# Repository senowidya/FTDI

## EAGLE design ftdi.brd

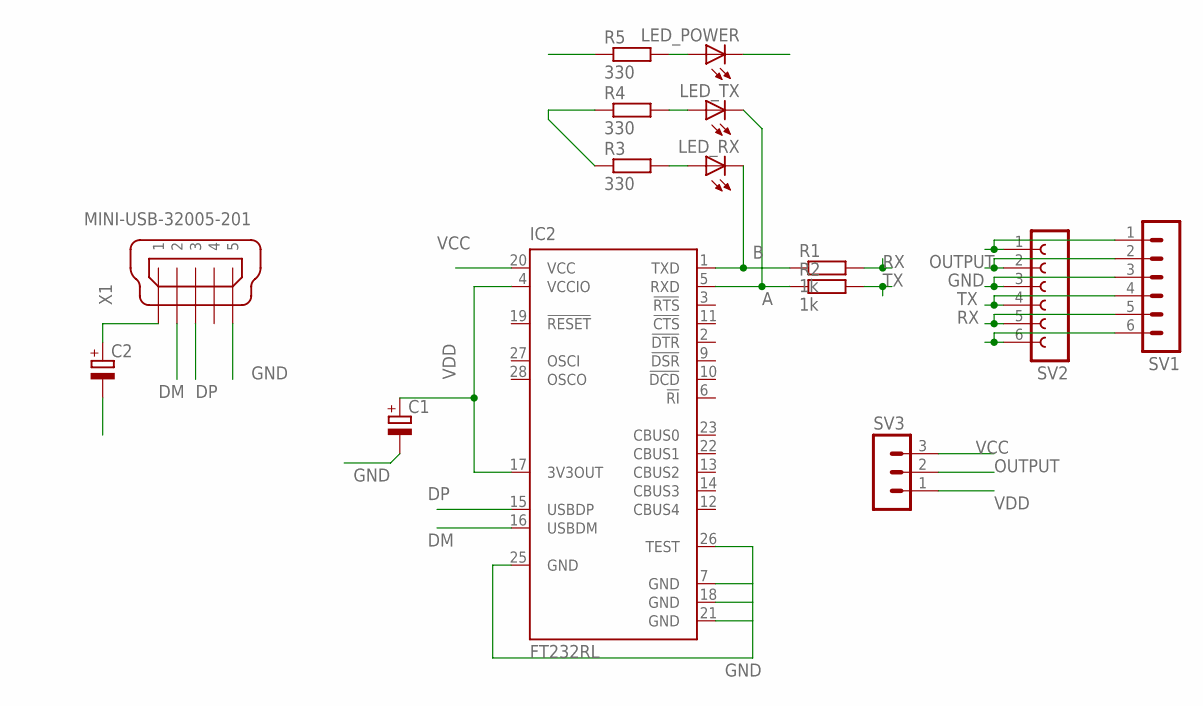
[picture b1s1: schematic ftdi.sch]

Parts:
C1, C2: CPOL-EUE2.5-5; E2,5-5
IC2: FT232RL; SSOP28
LED_POWER: LED3MM
LED_RX: LED3MM
LED_TX: LED3MM
R1, R2: 1k; 0204/7
R3, R4, R5: 330; 0204/7
SV1: MA06-1
SV2: FE06-1; FE06
SV3: MA03-1
X1: MINI-USB-32005-201; 32005-201

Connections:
A: IC2.5 (RXD), LED_TX.K (C), R2.1
B: IC2.1 (TXD), LED_RX.K (C), R1.1
DM: IC2.16 (USBDM), X1.2
DP: IC2.15 (USBDP), X1.3
GND: C1.-, C2.-, IC2.7 (GND), IC2.18 (GND), IC2.21 (GND), IC2.25 (GND), IC2.26 (TEST), LED_POWER.K (C), SV1.3, SV2.3, X1.5
unnamed: LED_POWER.A, R5.2
unnamed: LED_TX.A, R4.2
unnamed: SV1.1, SV2.1
unnamed: LED_RX.A, R3.2
unnamed: SV1.6, SV2.6
OUTPUT: SV1.2, SV2.2, SV3.2
RX: R1.2, SV1.5, SV2.5
TX: R2.2, SV1.4, SV2.4
VCC: C2.+, IC2.20 (VCC), R5.1, SV3.3, X1.1
VDD: C1.+, IC2.4 (VCCIO), IC2.17 (3V3OUT), R3.1, R4.1, SV3.1

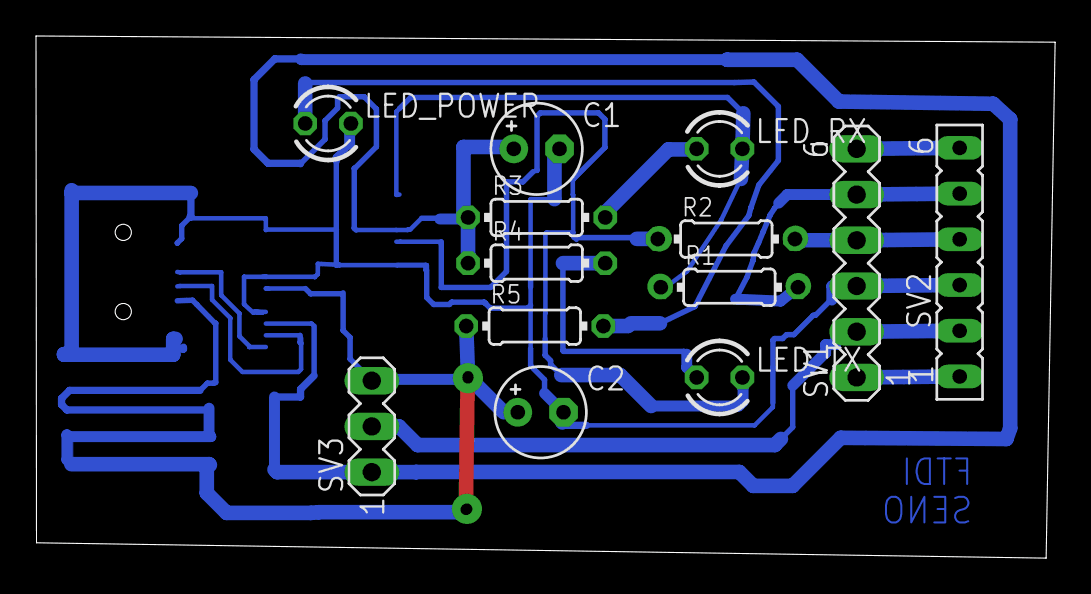
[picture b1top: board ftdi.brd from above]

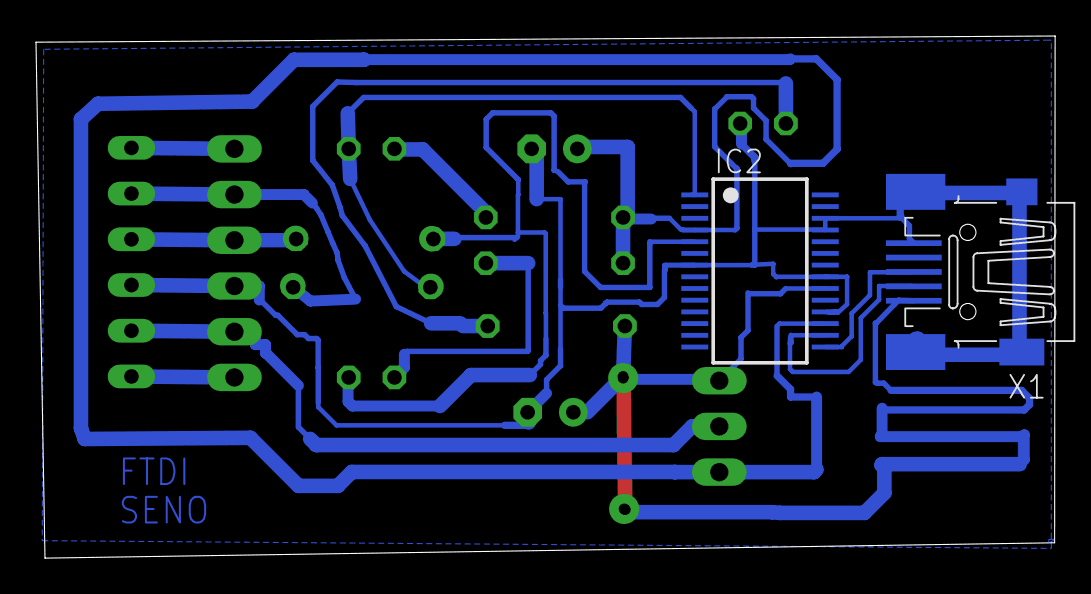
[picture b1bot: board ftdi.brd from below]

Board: 2 copper layers, 56.6 x 29.0 mm, 15 parts (2 on the bottom side), 15 nets.

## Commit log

2014-11-12 first release
